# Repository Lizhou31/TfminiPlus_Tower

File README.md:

# TfminiPlus_Tower

## An easy use distance sensors (Tfmini-plus) Tower
* Plug and Play
* Easy to Install

## TODO
* Add watchdog to prevent I2C connection error
* Add future extendible

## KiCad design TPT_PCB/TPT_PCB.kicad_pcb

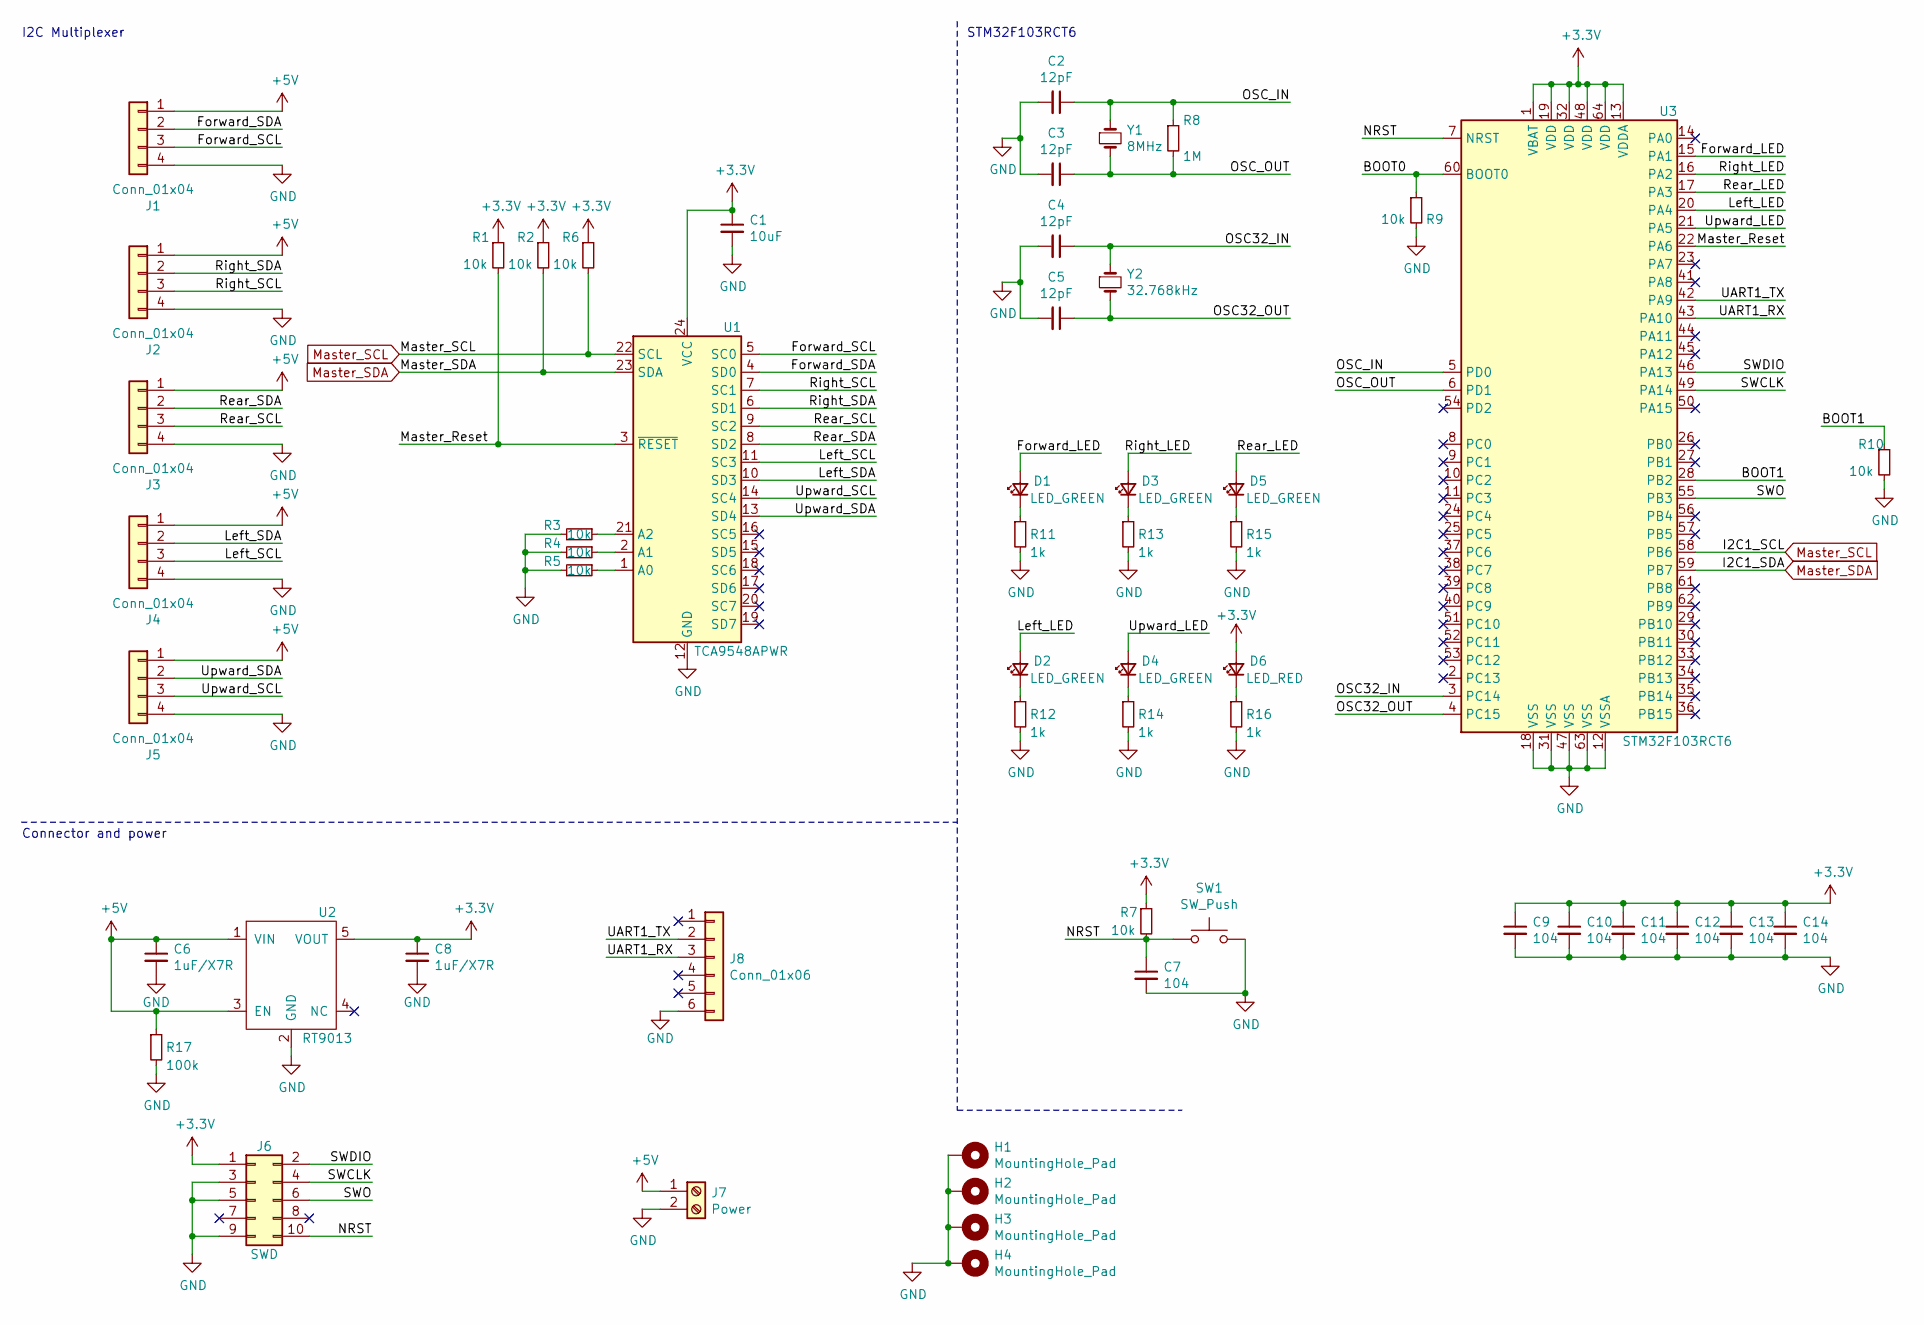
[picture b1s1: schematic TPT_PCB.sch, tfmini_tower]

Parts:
C1: 10uF; C_0805_2012Metric
C2, C3, C4, C5: 12pF; C_0805_2012Metric
C6, C8: 1uF/X7R; C_0805_2012Metric
C7, C9, C10, C11, C12, C13, C14: 104; C_0805_2012Metric
D1, D2, D3, D4, D5: LED_GREEN; LED_0805_2012Metric
D6: LED_RED; LED_0805_2012Metric
H1, H2, H3, H4: MountingHole_Pad; MountingHole_4.3mm_M4_Pad_Via
J1, J2, J3, J4: Conn_01x04; JST_GH_SM04B-GHS-TB_1x04-1MP_P1.25mm_Horizontal
J5: Conn_01x04; JST_GH_BM04B-GHS-TBT_1x04-1MP_P1.25mm_Vertical
J6: SWD; Samtec_HLE-105-02-xx-DV-TE_2x05_P2.54mm_Horizontal
J7: Power; TerminalBlock_Phoenix_PT-1,5-2-3.5-H_1x02_P3.50mm_Horizontal
J8: Conn_01x06; JST_GH_SM06B-GHS-TB_1x06-1MP_P1.25mm_Horizontal
R1, R2, R3, R4, R5, R6, R7, R9, R10: 10k; R_0805_2012Metric
R8: 1M; R_0805_2012Metric
R11, R12, R13, R14, R15, R16: 1k; R_0805_2012Metric
R17: 100k; R_0805_2012Metric
SW1: SW_Push; SW_Push_1P1T_NO_6x6mm_H9.5mm
U1: TCA9548APWR; TSSOP-24_4.4x7.8mm_P0.65mm
U2: RT9013; SOT94P279X129-5N
U3: STM32F103RCT6; LQFP-64_10x10mm_P0.5mm
Y1: 8MHz; XTAL_ABLS-8.000MHZ-B2-T
Y2: 32.768kHz; XTAL_AB26TRB-32.768KHZ-T

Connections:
+3V3: C1.1, C8.1, C9.1, C10.1, C11.1, C12.1, C13.1, C14.1, D6.2 (A), J6.1, R1.1, R2.1, R6.1, R7.1, U1.24 (VCC), U2.5 (VOUT), U3.1 (VBAT), U3.13 (VDDA), U3.19 (VDD), U3.32 (VDD), U3.48 (VDD), U3.64 (VDD)
+5V: C6.1, J1.1, J2.1, J3.1, J4.1, J5.1, J7.1, R17.1, U2.1 (VIN), U2.3 (EN)
/BOOT0: R9.1, U3.60 (BOOT0)
/BOOT1: R10.1, U3.28 (PB2)
/Forward_LED: D1.2 (A), U3.15 (PA1)
/Forward_SCL: J1.3, U1.5 (SC0)
/Forward_SDA: J1.2, U1.4 (SD0)
/Left_LED: D2.2 (A), U3.20 (PA4)
/Left_SCL: J4.3, U1.11 (SC3)
/Left_SDA: J4.2, U1.10 (SD3)
/Master_Reset: R1.2, U1.3 (~RESET), U3.22 (PA6)
/NRST: C7.1, J6.10, R7.2, SW1.1, U3.7 (NRST)
/OSC32_IN: C4.1, U3.3 (PC14), Y2.1
/OSC32_OUT: C5.1, U3.4 (PC15), Y2.2
/OSC_IN: C2.1, R8.1, U3.5 (PD0), Y1.1
/OSC_OUT: C3.1, R8.2, U3.6 (PD1), Y1.2
/Rear_LED: D5.2 (A), U3.17 (PA3)
/Rear_SCL: J3.3, U1.9 (SC2)
/Rear_SDA: J3.2, U1.8 (SD2)
/Right_LED: D3.2 (A), U3.16 (PA2)
/Right_SCL: J2.3, U1.7 (SC1)
/Right_SDA: J2.2, U1.6 (SD1)
/SWCLK: J6.4, U3.49 (PA14)
/SWDIO: J6.2, U3.46 (PA13)
/SWO: J6.6, U3.55 (PB3)
/UART1_RX: J8.3, U3.43 (PA10)
/UART1_TX: J8.2, U3.42 (PA9)
/Upward_LED: D4.2 (A), U3.21 (PA5)
/Upward_SCL: J5.3, U1.14 (SC4)
/Upward_SDA: J5.2, U1.13 (SD4)
GND: C1.2, C2.2, C3.2, C4.2, C5.2, C6.2, C7.2, C8.2, C9.2, C10.2, C11.2, C12.2, C13.2, C14.2, H1.1, H2.1, H3.1, H4.1, J1.4, J2.4, J3.4, J4.4, J5.4, J6.3, J6.5, J6.9, J7.2, J8.6, R3.2, R4.2, R5.2, R9.2, R10.2, R11.2, R12.2, R13.2, R14.2, R15.2, R16.2, R17.2, SW1.2, U1.12 (GND), U2.2 (GND), U3.12 (VSSA), U3.18 (VSS), U3.31 (VSS), U3.47 (VSS), U3.63 (VSS)
Master_SCL: R6.2, U1.22 (SCL), U3.58 (PB6)
Master_SDA: R2.2, U1.23 (SDA), U3.59 (PB7)
unnamed: D1.1 (K), R11.1
unnamed: D2.1 (K), R12.1
unnamed: D3.1 (K), R13.1
unnamed: D4.1 (K), R14.1
unnamed: D5.1 (K), R15.1
unnamed: D6.1 (K), R16.1
unnamed: R3.1, U1.21 (A2)
unnamed: R4.1, U1.2 (A1)
unnamed: R5.1, U1.1 (A0)

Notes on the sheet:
I2C Multiplexer
Connector and power
STM32F103RCT6

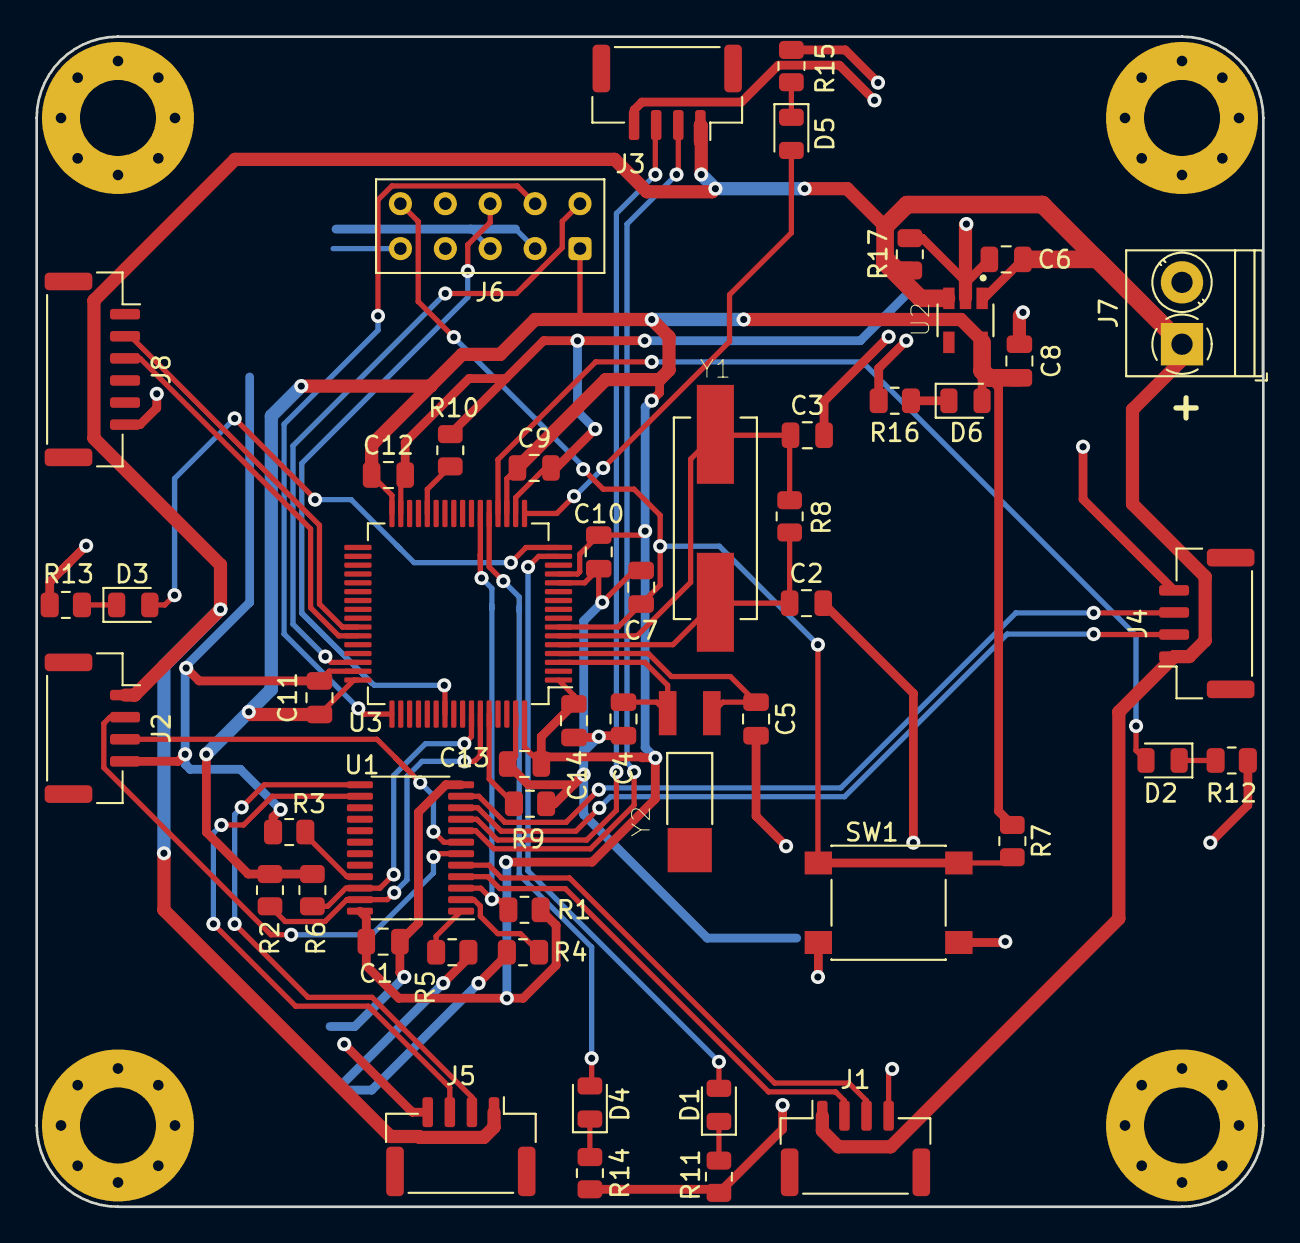
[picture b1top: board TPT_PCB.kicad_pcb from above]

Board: 2 copper layers, 69.4 x 66.2 mm, 55 parts (0 on the bottom side), 42 nets.

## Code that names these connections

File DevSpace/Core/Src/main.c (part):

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
  LL_APB2_GRP1_EnableClock(LL_APB2_GRP1_PERIPH_GPIOB);
  /**I2C1 GPIO Configuration
  PB6   ------> I2C1_SCL
  PB7   ------> I2C1_SDA
  */
  GPIO_InitStruct.Pin = LL_GPIO_PIN_6 | LL_GPIO_PIN_7;
  GPIO_InitStruct.Mode = LL_GPIO_MODE_ALTERNATE;
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
  LL_APB2_GRP1_EnableClock(LL_APB2_GRP1_PERIPH_GPIOA);
  /**USART1 GPIO Configuration
  PA9   ------> USART1_TX
  PA10   ------> USART1_RX
  */
  GPIO_InitStruct.Pin = LL_GPIO_PIN_9;
  GPIO_InitStruct.Mode = LL_GPIO_MODE_ALTERNATE;
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
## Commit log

2021-03-19 tfmini_plus use i2c
2021-03-19 add mavlink c_library_v2
2021-03-20 add uart transmit support
2021-03-22 add mavlink_v2 lib and use uart transmit
2021-03-24 fix over malloc cause hardfault
2021-03-25 not use malloc
2021-04-10 20210410 temp commit
2021-04-10 first test ok
2021-04-12 change tfmini read cmd with i2c multiplexer
2021-04-12 fix conflict
2021-04-12 add sensor scan
2021-04-14 fix wrong systemtick, add reset pin and led toggle
2021-04-14 fix some strange error, add minmum distance limit
2021-04-14 Edit README
2021-04-16 add iwdg,but havn't used. TODO:fix unbounded range
2021-04-17 修改當空曠區域時的0值問題
2021-04-19 a layout nood add PCB layout file
2021-04-19 change i2c standard mode to fast mode
2021-04-26 update pcb layout, but there are some problem. Must be re-do.
2021-04-28 re-layout and generate gbr file
2021-04-28 add boom
2021-06-17 修改PCB錯誤標示
2021-07-03 修正PCB文字層錯誤
2021-07-03 fix wrong component id
2021-07-06 change SWD connector add layout TODO list
2021-08-17 some pcb change
2021-08-17 optimize i2c and tfmini-plus lib

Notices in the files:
DevSpace/Core/Src/main.c:
© Copyright (c) 2021 STMicroelectronics.
All rights reserved.
This software component is licensed by ST under BSD 3-Clause license,
the "License"; You may not use this file except in compliance with the
License. You may obtain a copy of the License at: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
(C) COPYRIGHT STMicroelectronics *****END OF FILE
